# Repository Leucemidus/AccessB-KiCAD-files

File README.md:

# AccessB-KiCAD-files

This KiCAD project was made with KiCAD version 4.0.7.

The schematic and PCB design are NOT final, I need to make some changes:

*Change the footprint of the PIC, from SOIC_28_narrow to SOIC_28_Wide
*Relocate C3, this because PICkit 3 programmer hit it when is inserted on ICSP jumper
*Change and add silk screen notes on the PCB.
*a LOT of other things that I'm sure will appear....

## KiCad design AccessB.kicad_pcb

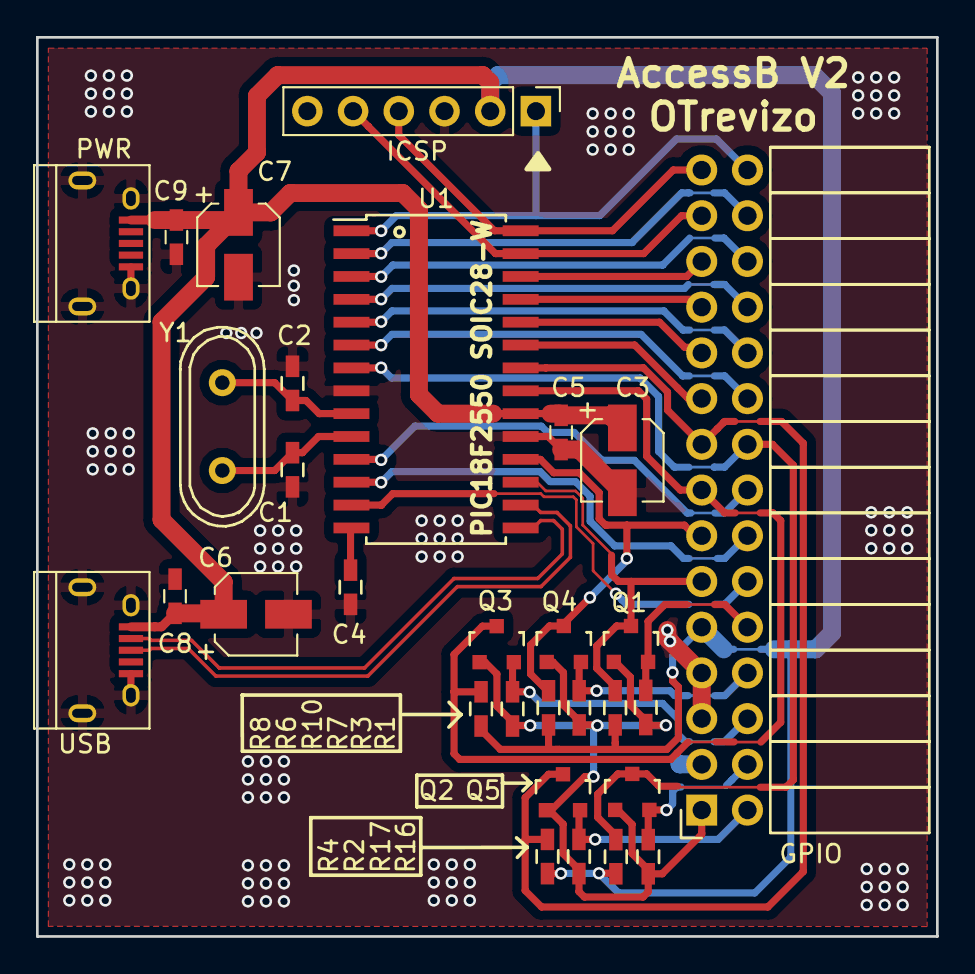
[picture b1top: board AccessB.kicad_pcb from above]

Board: 2 copper layers, 50.0 x 50.0 mm, 30 parts (0 on the bottom side), 33 nets.

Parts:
C1, C2: 20pF; C_0603_HandSoldering
C3, C6, C7: 10uF; CP_Elec_4x5.8
C4: 470pF; C_0603_HandSoldering
C5, C8, C9: 100pF; C_0603_HandSoldering
GPIO: GPIO; Socket_Strip_Angled_2x15
ICSP: ICSP; Pin_Header_Straight_1x06_Pitch2.54mm
PWR: USB_OTG; USB_Micro-B
Q1, Q2, Q3, Q4, Q5: BSS138; SOT-23
R1, R2, R3, R4, R6, R7, R8, R10, R16, R17: 10k; C_0603_HandSoldering
U1: PIC18(L)F2550-I/SO; SOIC-28W_7.5x17.9mm_Pitch1.27mm
USB: USB_OTG; USB_Micro-B
Y1: 4MHz; Crystal_HC49-U_Vertical

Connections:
+5V: C3.1, C5.1, C6.1, C7.1, C8.1, C9.1, GPIO.9, ICSP.2, PWR.1, R3.1, R4.1, R8.1, R10.1, R17.1, U1.20, USB.1
/D+: U1.16, USB.3
/D-: U1.15, USB.2
/GPIO0/RE3: GPIO.30, ICSP.1, U1.1
/GPIO1/RC0: GPIO.16, U1.11
/GPIO2/RC1: GPIO.14, U1.12
/GPIO3/RC2: GPIO.12, U1.13
/GPIO4/RC6: GPIO.11, Q1.3, R3.2, U1.17
/GPIO4/RC6_VLS: GPIO.10, Q1.2, R1.2
/GPIO5/RC7: GPIO.13, Q4.3, R10.2, U1.18
/GPIO5/RC7_VLS: GPIO.8, Q4.2, R7.2
/GPIO6/RA0: GPIO.28, U1.2
/GPIO7/RA1: GPIO.26, U1.3
/GPIO8/RA2: GPIO.24, U1.4
/GPIO9/RA3: GPIO.22, U1.5
/GPIO10/RA4: GPIO.20, U1.6
/GPIO11/RA5: GPIO.18, Q5.3, R17.2, U1.7
/GPIO11/RA5_VLS: GPIO.4, Q5.2, R16.2
/GPIO12/RB0: GPIO.15, Q3.3, R8.2, U1.21
/GPIO12/RB0_VLS: GPIO.6, Q3.2, R6.2
/GPIO13/RB1: GPIO.17, Q2.3, R4.2, U1.22
/GPIO13/RB1_VLS: GPIO.2, Q2.2, R2.2
/GPIO14/RB2: GPIO.19, U1.23
/GPIO15/RB3: GPIO.21, U1.24
/GPIO16/RB4: GPIO.23, U1.25
/GPIO17/RB5: GPIO.25, U1.26
/GPIO18/RB6: GPIO.27, ICSP.5, U1.27
/GPIO19/RB7: GPIO.29, ICSP.4, U1.28
/VLS: GPIO.1, Q1.1, Q2.1, Q3.1, Q4.1, Q5.1, R1.1, R2.1, R6.1, R7.1, R16.1
GND: C1.2, C2.2, C3.2, C4.2, C5.2, C6.2, C7.2, C8.2, C9.2, GPIO.3, GPIO.5, GPIO.7, ICSP.3, PWR.5, PWR.6, U1.8, U1.19, USB.5, USB.6
unnamed: C1.1, U1.10, Y1.2
unnamed: C2.1, U1.9, Y1.1
unnamed: C4.1, U1.14

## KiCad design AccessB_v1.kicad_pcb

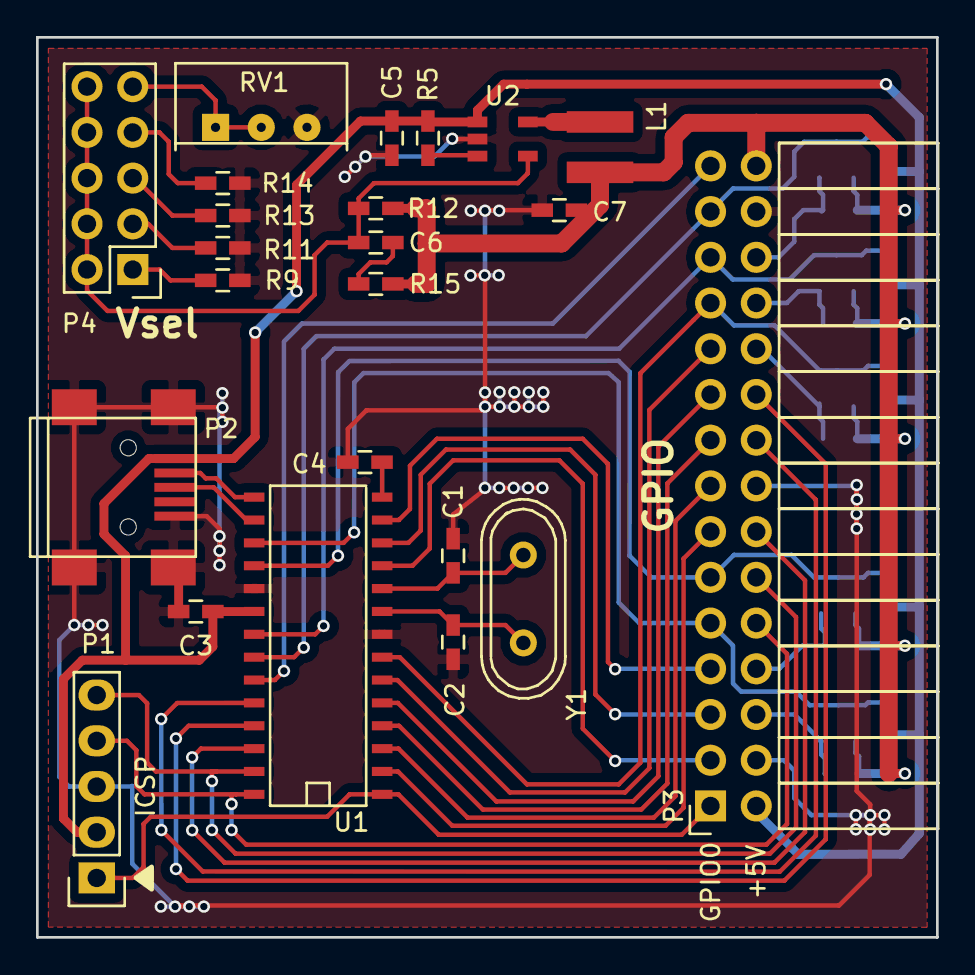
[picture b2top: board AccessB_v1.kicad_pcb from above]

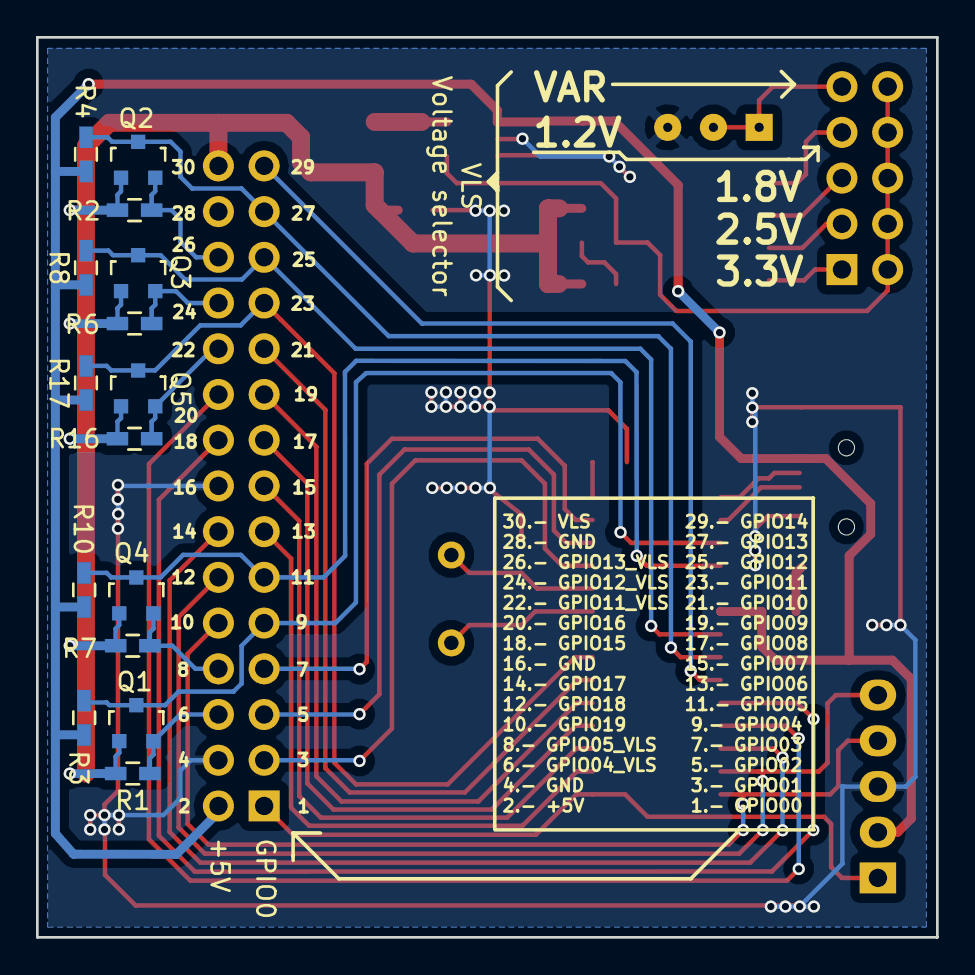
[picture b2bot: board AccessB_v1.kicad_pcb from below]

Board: 2 copper layers, 50.0 x 50.0 mm, 38 parts (15 on the bottom side), 42 nets.

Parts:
C1, C2: 20pF; C_0603_HandSoldering
C3: 10uF; C_0603_HandSoldering
C4: 470pF; C_0603_HandSoldering
C5, C7: 4.7uF; C_0603_HandSoldering
C6: 33pF; C_0603_HandSoldering
L1: 4.7uH; Inductor_NR4018_SMD_footprint
P1: ICSP; Pin_Header_Straight_1x05
P2: USB_OTG; USB_Mini-B
P3: GPIO; Socket_Strip_Angled_2x15
P4: Vsel; Pin_Header_Straight_2x05
Q1, Q2, Q3, Q4, Q5: BSS138; SOT-23
R1, R2, R3, R4, R6, R7, R8, R10, R16, R17: 10k; C_0603_HandSoldering
R5: 499k; C_0603_HandSoldering
R9: 63.4k; C_0603_HandSoldering
R11: 93.1k; C_0603_HandSoldering
R12: 200k; C_0603_HandSoldering
R13: 160k; C_0603_HandSoldering
R14: 402k; C_0603_HandSoldering
R15: 4.99k; C_0603_HandSoldering
RV1: 16M; Potentiometer_Trimmer-Suntan-TSR-3386C
U1: PIC18(L)F2550-I/SO; SOIC-28
U2: MCP1603BT-ADJI/OS; 5-TSOT
Y1: 4MHz; Crystal_HC49-U_Vertical

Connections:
+5V: C3.1, C5.1, P1.2, P2.1, P3.2, R3.1, R4.1, R5.1, R8.1, R10.1, R17.1, U1.20, U2.1
/AccessB Voltage Level Shifter/GPIO4/RC6: P3.9, Q1.3, R3.2, U1.17
/AccessB Voltage Level Shifter/GPIO4/RC6_VLS: P3.6, Q1.2, R1.2
/AccessB Voltage Level Shifter/GPIO5/RC7: P3.11, Q4.3, R10.2, U1.18
/AccessB Voltage Level Shifter/GPIO5/RC7_VLS: P3.8, Q4.2, R7.2
/AccessB Voltage Level Shifter/GPIO11/RA5: P3.23, Q5.3, R17.2, U1.7
/AccessB Voltage Level Shifter/GPIO11/RA5_VLS: P3.22, Q5.2, R16.2
/AccessB Voltage Level Shifter/GPIO12/RB0: P3.25, Q3.3, R8.2, U1.21
/AccessB Voltage Level Shifter/GPIO12/RB0_VLS: P3.24, Q3.2, R6.2
/AccessB Voltage Level Shifter/GPIO13/RB1: P3.27, Q2.3, R4.2, U1.22
/AccessB Voltage Level Shifter/GPIO13/RB1_VLS: P3.26, Q2.2, R2.2
/AccessB Voltage Level Shifter/VLS: C7.1, L1.2, P3.30, Q1.1, Q2.1, Q3.1, Q4.1, Q5.1, R1.1, R2.1, R6.1, R7.1, R12.1, R15.1, R16.1
/D+/RC5: P2.3, U1.16
/D-/RC4: P2.2, U1.15
/GPIO0/RE3: P1.1, P3.1, U1.1
/GPIO1/RC0: P3.3, U1.11
/GPIO2/RC1: P3.5, U1.12
/GPIO3/RC2: P3.7, U1.13
/GPIO6/RA0: P3.13, U1.2
/GPIO7/RA1: P3.15, U1.3
/GPIO8/RA2: P3.17, U1.4
/GPIO9/RA3: P3.19, U1.5
/GPIO10/RA4: P3.21, U1.6
/GPIO14/RB2: P3.29, U1.23
/GPIO15/RB3: P3.18, U1.24
/GPIO16/RB4: P3.20, U1.25
/GPIO17/RB5: P3.14, U1.26
/GPIO18/RB6: P1.5, P3.12, U1.27
/GPIO19/RB7: P1.4, P3.10, U1.28
GND: C1.2, C2.2, C3.2, C4.2, C5.2, C7.2, P1.3, P2.5, P2.6, P3.4, P3.16, P3.28, R9.2, R11.2, R13.2, R14.2, RV1.3, U1.8, U1.19, U2.2
unnamed: C1.1, U1.10, Y1.2
unnamed: C2.1, U1.9, Y1.1
unnamed: C4.1, U1.14
unnamed: C6.1, R15.2
unnamed: C6.2, P4.2, P4.4, P4.6, P4.8, P4.10, R12.2, U2.4
unnamed: L1.1, U2.5
unnamed: P4.1, R9.1
unnamed: P4.3, R11.1
unnamed: P4.5, R13.1
unnamed: P4.7, R14.1
unnamed: P4.9, RV1.1, RV1.2
unnamed: R5.2, U2.3

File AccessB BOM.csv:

"Id";"Identificador";"Empaquetado";"Cantidad";"Identificación";"Suministrador y ref";
1;"M2,M2,M2,M2";"MountingHole_2.2mm_M2_Pad_Via";4;"MountingHole_2.2mm_M2_Pad_Via";;;
2;"C1,C2";"C_0603_HandSoldering";2;"20pF";;;
3;"C4";"C_0603_HandSoldering";1;"470pF";;;
4;"C5,C7";"C_0603_HandSoldering";2;"4.7uF";;;
5;"C6";"C_0603_HandSoldering";1;"33pF";;;
6;"P3";"Socket_Strip_Angled_2x15";1;"GPIO";;;
7;"P4";"Pin_Header_Straight_2x05";1;"Vsel";;;
8;"Q1,Q2,Q3,Q4,Q5";"SOT-23";5;"BSS138";;;
9;"R1,R2,R3,R4,R6,R7,R8,R10,R16,R17";"C_0603_HandSoldering";10;"10k";;;
10;"R5";"C_0603_HandSoldering";1;"499k";;;
11;"R9";"C_0603_HandSoldering";1;"63.4k";;;
12;"R11";"C_0603_HandSoldering";1;"93.1k";;;
13;"R12";"C_0603_HandSoldering";1;"200k";;;
14;"R13";"C_0603_HandSoldering";1;"160k";;;
15;"R14";"C_0603_HandSoldering";1;"402k";;;
16;"R15";"C_0603_HandSoldering";1;"4.99k";;;
17;"RV1";"Potentiometer_Trimmer-Suntan-TSR-3386C";1;"16M";;;
18;"U1";"SOIC-28";1;"PIC18(L)F2550-I/SO";;;
19;"U2";"5-TSOT";1;"MCP1603BT-ADJI/OS";;;
20;"Y1";"Crystal_HC49-U_Vertical";1;"4MHz";;;
21;"L1";"Inductor_NR4018_SMD_footprint";1;"4.7uH";;;
22;"P2,P5";"USB_Micro-B";2;"USB_OTG";;;
23;"C3,C8";"CP_Elec_4x5.8";2;"10uF";;;
24;"P1";"Pin_Header_Straight_1x06_Pitch2.54mm";1;"ICSP";;;
25;"REF**";"SOIC-28W_7.5x17.9mm_Pitch1.27mm";1;"SOIC-28W_7.5x17.9mm_Pitch1.27mm";;;

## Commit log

2018-09-25 KiCAD files
    These are the files for KiCAD design project for AccessB.
2018-09-25 KiCAD design files for AccessB PCB
2018-10-24 Update
    PCB update in progress
2018-10-24 Update
    PCB update.
2018-10-26 Updates
    ...
2018-10-26 Again updates
    ...
2018-10-29 update again
2018-11-01 another upd
2018-11-07 New update
    update
2018-11-07 update
    update
2018-11-09 almost end
2018-11-09 Update
    Some reworking....
2018-11-12 more
2018-11-12 Update
    Only need to do routing of USB D+/D- Differential pair.
2018-11-12 sdf
    df
2018-11-15 another update
    dfd
2018-11-15 update
    sdgsfd
2018-11-20 updat
2018-11-20 Maybe the final version...
    Maybe....??
